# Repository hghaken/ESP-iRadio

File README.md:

# ESP32 Internet Radio

Battery-powered internet radio on an Olimex ESP32-DevKit-LiPo (WROVER, PSRAM): streams AAC/MP3 internet
radio over WiFi and plays it on Bluetooth headphones or a Bluetooth speaker (A2DP source), with a small colour TFT status
display (1.69" IPS, ST7789, 280x240: station logo, station, artist and song with scrolling for long lines,
Bluetooth link quality, buffer, WiFi signal, battery; high-contrast colours, no flicker; brightness,
night mode and idle dimming; a progress screen during firmware updates) and a web page for control,
configuration (up to 60 stations), diagnostics and firmware updates.

- Firmware: Arduino (C++) with PlatformIO. Build with `pio run`; update the running radio over WiFi with
  `pio run -t upload` (or upload `firmware.bin` on the web page). Serial flashing (`pio run -e usb -t upload`)
  is only needed once, for the OTA partition table. The firmware uses ~85% of an OTA slot (env `radio`) or ~74% (env `idf`); older
  builds are kept as git tags and in the git-ignored `backup/firmware/` for a quick rollback over WiFi.
- Live log: the web page has a "Log" section with an on/off switch that shows everything the radio
  also prints on the USB serial port (last ~64 KB kept, download as a text file), so the USB
  connector can stay on a power bank.
- Experimental: env `idf` builds Arduino as an ESP-IDF component with an own SDK configuration
  (`scripts/build_idf.ps1`, see `docs/framework-build.md`): classic Bluetooth only, no BLE/SPP/HFP,
  Bluetooth heap in PSRAM. ~74% of the OTA slot instead of ~85%, ~28 KB more free internal RAM. This
  is the build that runs on the radio. A larger TCP window was tried and did not work next to Bluetooth.
- First boot: join the access point `ESP-iRadio-Setup`, pick your WiFi network; afterwards use
  `http://radio.local/`.
- Bluetooth devices: up to 4 remembered (headphones, speakers), one plays at a time; play/pause on the device mutes, twice = next station, three times = previous. Pair a new
  one from the web page (device in pairing mode, type its name). Automatic mode tries them in the
  order you set (arrows); otherwise pick one with "Use" (restart, ~30 s). The radio reconnects
  with WiFi held off until the page finishes. "Try again" pages again and wipes nothing.
- SD card (microSD breakout on the SPI bus, CS GPIO4): daily log and measurement files with a chart
  on the web page, settings backup/restore, 64x64 station logos, copies of working firmware to roll
  back without a PC, and a year of history (events, listening and stream statistics per station,
  crash dumps) with tables on the web page.
- Rotary encoder (EC11): turn for volume (a bar on the display), press to mute, hold to choose a
  station.
- Line output and speaker: with Bluetooth switched off the radio plays on a PCM5102A I2S DAC
  (3.5 mm line out) and a MAX98357A I2S amplifier for a small speaker (web checkbox "Speaker").
- PCB: the KiCad project in `KiCad/` holds the schematic of an integrated board (ESP32-WROVER-IE,
  USB-C with charger and cell protection, display panel, DAC, amplifier, microSD, encoder, all
  parts assembled by JLCPCB); no board layout yet. See `KiCad/README.md`.
- WiFi: the radio reconnects to the mesh point it last used. A minute after every connect, and
  whenever the signal stays under a threshold on the web page (default -65 dBm), it looks for a
  point at least 12 dB stronger and moves there. The "Search" list shows every mesh point (channel,
  BSSID) with a "Switch to this access point" button. Opening the page does not scan
  for networks unless "Search networks when the page opens" is on. Setup mode always scans.
- Battery: 5000 mAh Li-Po (~28 h expected; a 2500 mAh cell ran ~14 h); level shown on the display
  and the web page.
- Stations: plain `http://` AAC-LC or MP3 streams (no TLS). About 25 Dutch stations (NPO, Radio 10,
  Veronica, Qmusic, Arrow) are verified; the URLs and the rules for finding working ones are in
  AGENTS.md under "Stations". Stations that are too heavy, HE-AAC only or https-only (Joe, NPO
  Sterren.nl, RadioNL, Team FM) run through Liquidsoap relays on a NAS (`nas/`) that re-encode
  them to AAC-LC 96 kbps on the own Icecast server.

All project knowledge - hardware, wiring, build and update commands, and the pitfalls learned the hard way
(internal RAM, flash budget, WiFi/Bluetooth coexistence, headphone pairing, brownouts) - lives in
[AGENTS.md](AGENTS.md).

## Hardware documentation

Not included in this repository (third-party documents); get them from the makers:
- Olimex ESP32-DevKit-LiPo: product page and user manual at https://www.olimex.com/Products/IoT/ESP32/ESP32-DevKit-LiPo/ ,
  schematics and KiCad files at https://github.com/OLIMEX/ESP32-DevKit-LiPo
  (`docs/olimex-jumpers-bottom.png` is drawn from that KiCad layout).
- 1.69" ST7789 IPS module (240x280, e.g. ZJY169S0800TG01) and a generic SPI microSD breakout.
- Sony WH-1000XM6 help guide: https://helpguide.sony.net/

## Credits and licence

Built with PlatformIO and the Arduino core for the ESP32, and these libraries:
[ESP32-A2DP](https://github.com/pschatzmann/ESP32-A2DP) (Apache-2.0),
[arduino-audio-tools](https://github.com/pschatzmann/arduino-audio-tools) (GPL-3.0),
[arduino-libhelix](https://github.com/pschatzmann/arduino-libhelix) (GPL-3.0, Helix AAC/MP3 decoders),
[Adafruit GFX](https://github.com/adafruit/Adafruit-GFX-Library) (BSD) and
[Adafruit ST7735 and ST7789](https://github.com/adafruit/Adafruit-ST7735-Library) (MIT).
The NAS relays use [Liquidsoap](https://www.liquidsoap.info/) and [Icecast](https://icecast.org/).

This project is licensed under the GNU General Public License v3.0, see [LICENSE](LICENSE).
Station URLs are examples of public Dutch broadcasters; host names such as `icecast.example.com`
and `my-nas` stand for your own servers.

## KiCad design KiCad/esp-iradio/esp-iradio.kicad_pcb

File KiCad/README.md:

# KiCad: PCB for the ESP iRadio

This folder holds everything an AI agent (Claude, Grok, ...) or a person needs to design a printed
circuit board for this radio in **KiCad 9**. The KiCad project is `esp-iradio/`: **schematic Rev B
of the integrated board** (2026-10-15, two A3 sheets in Elektuur/Elektor style, generated by the
scripts in `esp-iradio/tools/`; layout **Rev C** of 2026-10-16: 122 x 76 mm, 4 layers, autorouted,
DRC clean, for hand assembly (1206 passives) with display, encoder and connectors from top to
bottom, RCA outputs next to the 3.5 mm jack; the earlier 80 x 60 and 90 x 60 layouts (Rev B) were
reviewed by Grok and Claude). Its status, decisions, libraries and the
checks still open before the layout are in `esp-iradio/NOTES.md`.

## What the board is

Today the radio is a hand-wired stack: an **Olimex ESP32-DevKit-LiPo** (ESP32-WROVER, Li-Po charger,
USB) with jumper wires to a 1.69" ST7789 display. A rotary encoder, a microSD socket, a PCM5102A
DAC (line out) and a MAX98357A I2S amplifier (speaker) work on the breadboard (2026-10-15).

**Phase 1 (2026-10-11 .. 10-15, superseded): a carrier board.** The Olimex board plugs in on two
1x19 pin headers; the carrier holds the display, the encoder, the microSD socket, a PCM5102A DAC chip
(line out on a 3.5 mm jack), a mono class-D amplifier chip for one speaker, and a USB-C power
input. The firmware needs no pin changes: every net in `02-pinout-and-nets.md` matches
`src/config.h` and the docs. 2-layer board, assembled by JLCPCB; the ESP32 module and its charger
stay a finished product.

Owner decisions (2026-10-11, details in `01-requirements.md`): chips on the board (no audio
modules), display on the board, a 3D-printed case designed around the board, one mono speaker,
amplifier powered from a USB-C input, JLCPCB with SMT assembly.

**Phase 2 (chosen 2026-10-15, the current design, see `07-integrated-board.md`): an integrated
board** without breakouts: ESP32-WROVER-IE-N16R8 (external antenna on its U.FL), USB-C with a
CH340C, BQ24074 power-path charger with cell protection, 3.3 V LDO with the on/off switch, DAC,
amplifier, microSD and encoder, every part assembled by JLCPCB from stock; the display is the
HS20S010B module (2.0in, 320 x 240, LCSC C5329586) on two sockets, ordered loose in the same
JLCPCB/LCSC order (the bare 1.69in panel is not sold there). The owner chose to skip the carrier board. Documents 01-06 were written for
the carrier: their banners say what still applies.

## Files (read in this order)

| File | Content |
|---|---|
| `07-integrated-board.md` | **The current design input** (phase 2): owner decisions D8-D18, power (USB-C, BQ24074, cell protection, LDOs, switch), USB serial, WROVER-IE, display module, GPIO map, JLCPCB parts with LCSC numbers |
| `esp-iradio/NOTES.md` | Schematic Rev B: sheets, nets between them, chosen values, libraries, checks open before the layout |
| `esp-iradio/tools/README.md` | How the schematic is generated and checked (ERC, netlist check) |
| `06-checklist-and-bring-up.md` | Review checklist and bring-up: a section for the integrated board, then the carrier's |
| `01-requirements.md` | Scope, use cases and owner decisions D1-D7 (phase 1; most still hold) |
| `02-pinout-and-nets.md` | GPIO and net names (phase 1 headers; the GPIOs are the same on the integrated board, see 07) |
| `03-parts-and-footprints.md` | Phase 1 bill of materials (the integrated board's parts are in 07) |
| `04-power.md` | Phase 1 power tree (superseded by "Power" in 07) |
| `05-layout-guidelines.md` | Layout rules for the integrated board (rewritten 2026-10-15): mechanics, U.FL, 4 layers, USB pair, charger heat, audio and SPI routing, JLCPCB fab rules |

## Sources in this repository

- `AGENTS.md` (project root): the whole project, pin tables, pitfalls. Sections "Display wiring",
  "Battery measurement", "Hardware".
- `src/config.h`: the pins the firmware uses (`TFT_*`, `SD_CS`, `BAT_SENSE_PIN`, `PWR_SENSE_PIN`).
- `docs/speaker-output.md`: PCM5102A line out and MAX98357A speaker on the breadboard (pins, tests).
- `docs/display-research.md`: rotary encoder choice and pins.
- `docs/olimex-jumpers-bottom.png`: the three solder jumpers for battery/USB sensing on the Olimex board.
- Olimex ESP32-DevKit-LiPo **Rev.D** open hardware (KiCad sources, take the exact header
  positions, board outline and mounting holes from there):
  https://github.com/OLIMEX/ESP32-DevKit-LiPo/tree/master/HARDWARE

## Deliverables (when the design is done)

1. KiCad project `KiCad/esp-iradio/` (`.kicad_pro`, `esp-iradio.kicad_sch` + `power_usb.kicad_sch`,
   `.kicad_pcb`, project-local symbol/footprint libraries in `KiCad/esp-iradio/lib/`). Done so
   far: the schematic (Rev B).
2. Fabrication output in `KiCad/esp-iradio/fab/`: Gerbers + drill files, BOM (CSV with LCSC
   codes) and pick-and-place (CPL) file in JLCPCB's format.
3. For the 3D-printed case: a STEP of the assembled board and a DXF of the outline and holes in
   `KiCad/esp-iradio/case/`.
4. A short `KiCad/esp-iradio/NOTES.md`: design decisions, deviations from these documents, revision
   history (Rev A, B, ...).
5. If a pin changes: update `src/config.h`, `AGENTS.md`, the GPIO map in `07-integrated-board.md`
   and the schematic generator (`esp-iradio/tools/`) in the same step. The firmware and the board
   must never disagree.

## Tooling on the owner's PC (2026-10-11)

- **KiCad 9.0.9** (`C:\Program Files\KiCad\9.0`). Chosen over EasyEDA Pro for git-friendly text
  files and AI access; JLCPCB output comes from plugins.
- **KiCad MCP server** for Claude Code: mixelpixx/KiCAD-MCP-Server v2.8.2 (branch `stable`, MIT),
  cloned to `C:\Users\Admin\mcp-servers\KiCAD-MCP-Server`. Python: a venv in that folder (`venv\`,
  made from KiCad's own Python 3.11 with `--system-site-packages`, so `pcbnew` imports and the KiCad
  install itself stays untouched) with `requirements.txt`; the server finds the venv by itself.
  Node 24, `npm install` + `npm run build` -> `dist\index.js`. Registered in Claude Code at user
  scope as `kicad` (`claude mcp add kicad --scope user -e KICAD_AUTO_LAUNCH=false ... -- node
  ...\dist\index.js`); the tools appear in a new Claude Code session. Update: `git pull` in that
  folder, `npm run build`, `venv\Scripts\python -m pip install -r requirements.txt`.
- Pitfall: the server writes new sheets in the KiCad 10 file format, which KiCad 9 skips
  without an error (empty netlist). Its templates are patched to KiCad 9 on this PC; details and
  the fix in `esp-iradio/NOTES.md` ("Tooling pitfall"). Check every change with
  `kicad-cli sch export netlist` (component count) and `kicad-cli sch erc`.
- Optional, for live sync with an open KiCad window: KiCad -> Preferences -> Plugins -> enable
  the KiCad API (IPC). The file-based tools work without it.
- Installed in KiCad (Plugin and Content Manager): **kicad-jlcpcb-tools** (LCSC part search with
  stock, `LCSC` fields, JLCPCB BOM/CPL export; its parts database
  `E:\Documents\KiCad\9.0\3rdparty\plugins\com_github_bouni_kicad-jlcpcb-tools\jlcpcb\current-parts-fts5.db`
  is plain SQLite and can be queried read-only by a script). **easyeda2kicad** 1.0.1 (symbol,
  footprint and 3D model of an LCSC part) runs from a Python venv: `easyeda2kicad --lcsc_id
  C701352 --full --output <dir>/lcsc`; the project copy is `esp-iradio/lib/lcsc.*`.
- Rev B (schematic and first layout) was not drawn with the MCP server but generated by
  `esp-iradio/tools/` (Python; the board scripts run with KiCad's own Python, see its README).
- Autorouter: Freerouting 1.9.0 (`C:\Users\Admin\tools\freerouting-1.9.0.jar`) on a portable
  Java 21 (`C:\Users\Admin\tools\jdk-21.0.12.1+1-jre`), downloaded with the owner's consent
  2026-10-15. Freerouting 2.x jars need Java 25; the 2.5.0 native CLI crashed while routing.
- 3D models: this PC's KiCad install lacks some 3D folders (`Connector_USB`, `Rotary_Encoder`);
  install them before the STEP export for the case.

## Commands (`kicad-cli`, run inside `esp-iradio/`)

`C:\Program Files\KiCad\9.0\bin\kicad-cli.exe`:
- ERC: `kicad-cli sch erc --severity-all -o erc.rpt esp-iradio.kicad_sch`
- Netlist (check the component count after every schematic change):
  `kicad-cli sch export netlist --format kicadsexpr -o esp-iradio.net esp-iradio.kicad_sch`, then
  `python tools/intcheck.py esp-iradio.net` (expected connections of the integrated board)
- Schematic PDF/SVG: `kicad-cli sch export pdf esp-iradio.kicad_sch` (or `export svg -o <dir>`)
- DRC: `kicad-cli pcb drc esp-iradio.kicad_pcb`
- JLCPCB order files (Gerber zip, BOM, CPL): `"C:/Program Files/KiCad/9.0/bin/python.exe"
  tools/jlcfab.py` writes them to `esp-iradio/jlcpcb/` (see the README there).
- STEP for the case: `kicad-cli pcb export step esp-iradio.kicad_pcb -o case/esp-iradio.step`

Close the schematic/board in KiCad (or reload afterwards) before an agent edits the files: KiCad
overwrites external changes; `*.lck` files mean KiCad has them open. Only one agent session works
on the KiCad project at a time.

## Rules for agents

- Do not invent part numbers, LCSC codes or module dimensions: look them up (datasheet, supplier
  page) or mark them `TBD` and list them under open questions.
- Ask the owner before ordering anything or choosing between options marked "owner decides".
- Everything in this folder is English; talk to the owner in Dutch.

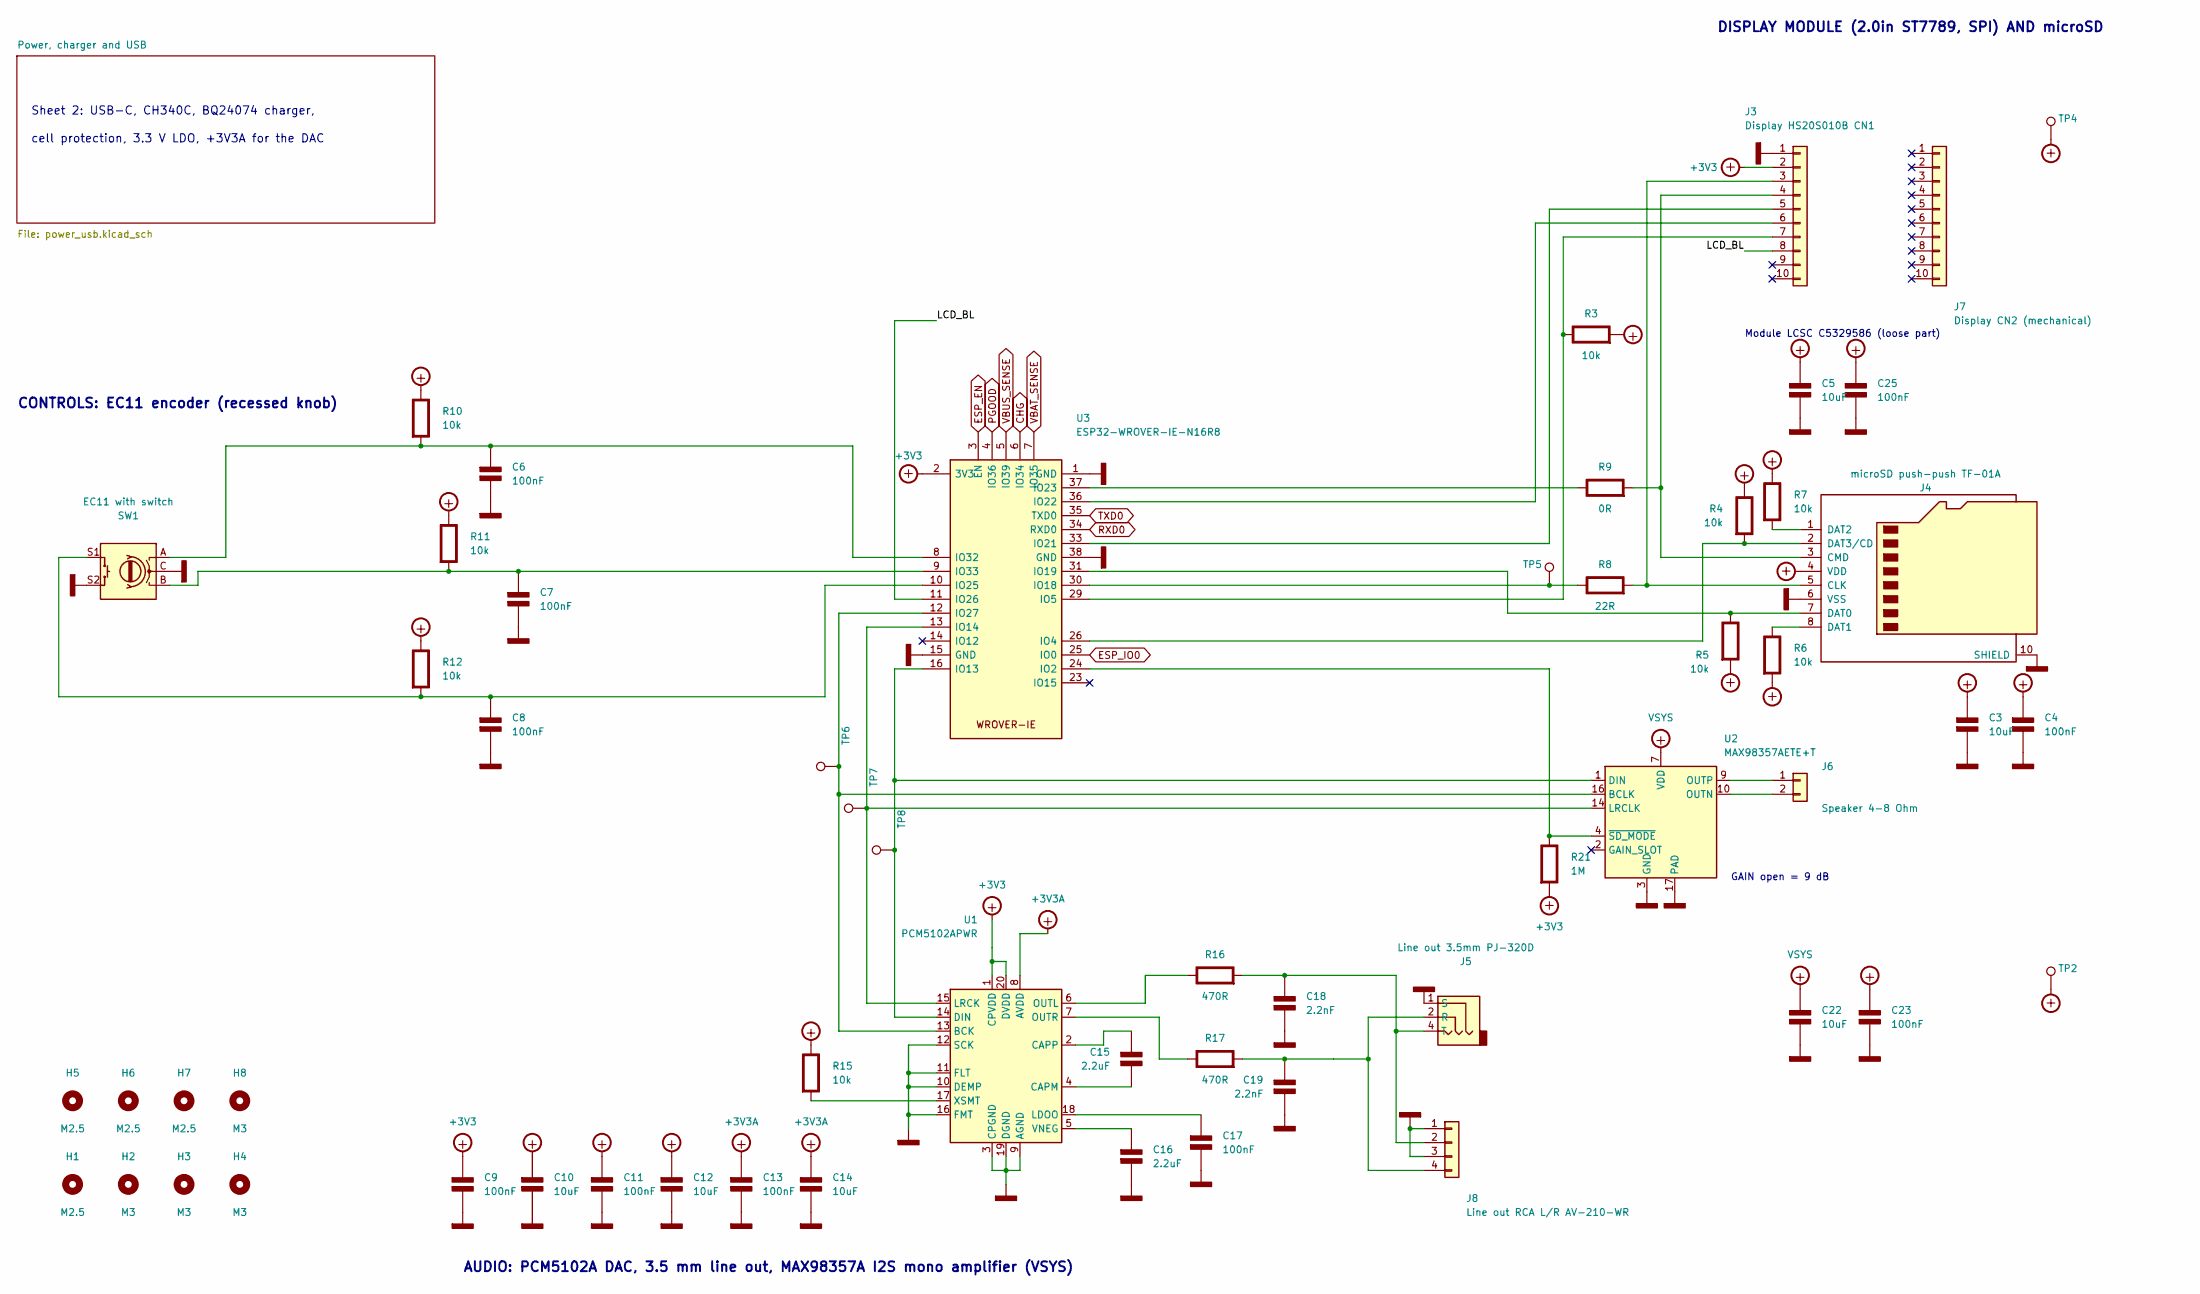
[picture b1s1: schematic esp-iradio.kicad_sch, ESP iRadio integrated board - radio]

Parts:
C3, C5, C10, C12, C14, C22: 10uF; C_1206_3216Metric
C4, C6, C7, C8, C9, C11, C13, C17, C23, C25: 100nF; C_1206_3216Metric
C15, C16: 2.2uF; C_1206_3216Metric
C18, C19: 2.2nF; C_1206_3216Metric
H1, H5, H6, H7: M2.5; MountingHole_2.7mm_M2.5
H2, H3, H4, H8: M3; MountingHole_3.2mm_M3
J3: Display HS20S010B CN1; PinSocket_1x10_P2.54mm_Vertical_HS20S010B; LCSC C2897373
J4: microSD push-push TF-01A; TF-SMD_TF-01A; LCSC C91145
J5: Line out 3.5mm PJ-320D; AUDIO-SMD_PJ-320D-1; LCSC C431535
J6: Speaker 4-8 Ohm; TerminalBlock_MaiXu_MX126-5.0-02P_1x02_P5.00mm; LCSC C8404
J7: Display CN2 (mechanical); PinSocket_1x10_P2.54mm_Vertical; LCSC C2897373
J8: Line out RCA L/R AV-210-WR; RCA-TH_AV-210-WR; LCSC C53431212
R3, R4, R5, R6, R7, R10, R11, R12, R15: 10k; R_1206_3216Metric
R8: 22R; R_1206_3216Metric
R9: 0R; R_1206_3216Metric
R16, R17: 470R; R_1206_3216Metric
R21: 1M; R_1206_3216Metric
SW1: EC11 with switch; RotaryEncoder_Alps_EC11E-Switch_Vertical_H20mm
TP2: VSYS; TestPoint_Pad_D1.5mm
TP4: +3V3; TestPoint_Pad_D1.5mm
TP5: SPI_SCK; TestPoint_Pad_D1.5mm
TP6: I2S_BCK; TestPoint_Pad_D1.5mm
TP7: I2S_LRCK; TestPoint_Pad_D1.5mm
TP8: I2S_DATA; TestPoint_Pad_D1.5mm
U1: PCM5102APWR; TSSOP-20_4.4x6.5mm_P0.65mm; LCSC C107671
U2: MAX98357AETE+T; TQFN-16-1EP_3x3mm_P0.5mm_EP1.23x1.23mm_ThermalVias; LCSC C910544
U3: ESP32-WROVER-IE-N16R8; ESP32-WROVER-IE_SMD; LCSC C701352

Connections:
+3V3: C3.1 (+), C4.1 (+), C5.1 (+), C9.1 (+), C10.1 (+), C11.1 (+), C12.1 (+), C25.1 (+), J3.2, J4.4 (VDD), R3.2 (-), R4.1 (+), R5.2 (-), R6.2 (-), R7.1 (+), R10.1 (+), R11.1 (+), R12.1 (+), R15.1 (+), R21.2 (-), TP4.1, U1.1 (CPVDD), U1.20 (DVDD), U3.2 (3V3); also elsewhere on the board
+3V3A: C13.1 (+), C14.1 (+), U1.8 (AVDD); also elsewhere on the board
/LCD_BL: J3.8, U3.11 (IO26)
CHG: U3.6 (IO34); also elsewhere on the board
ESP_EN: U3.3 (EN); also elsewhere on the board
ESP_IO0: U3.25 (IO0); also elsewhere on the board
GND: C3.2 (-), C4.2 (-), C5.2 (-), C6.2 (-), C7.2 (-), C8.2 (-), C9.2 (-), C10.2 (-), C11.2 (-), C12.2 (-), C13.2 (-), C14.2 (-), C16.2 (-), C17.2 (-), C18.2 (-), C19.2 (-), C22.2 (-), C23.2 (-), C25.2 (-), J3.1, J4.6 (VSS), J4.10 (SHIELD), J4.11 (SHIELD), J4.12 (SHIELD), J4.13 (SHIELD), J5.1 (S), J8.1, J8.3, SW1.C, SW1.S2, U1.3 (CPGND), U1.9 (AGND), U1.10 (DEMP), U1.11 (FLT), U1.12 (SCK), U1.16 (FMT), U1.19 (DGND), U2.3 (GND), U2.11 (GND), U2.15 (GND), U2.17 (PAD), U3.1 (GND), U3.15 (GND), U3.38 (GND), U3.39 (GND); also elsewhere on the board
unnamed: C6.1 (+), R10.2 (-), SW1.A, U3.8 (IO32)
unnamed: C7.1 (+), R11.2 (-), SW1.B, U3.9 (IO33)
unnamed: C8.1 (+), R12.2 (-), SW1.S1, U3.10 (IO25)
unnamed: C15.1 (+), U1.2 (CAPP)
unnamed: C15.2 (-), U1.4 (CAPM)
unnamed: C16.1 (+), U1.5 (VNEG)
unnamed: C17.1 (+), U1.18 (LDOO)
unnamed: C18.1 (+), J5.4 (T), J8.2, R16.2 (-)
unnamed: C19.1 (+), J5.2 (R), J8.4, R17.2 (-)
unnamed: J3.3, J4.5 (CLK), R8.2 (-)
unnamed: J3.4, J4.3 (CMD), R9.2 (-)
unnamed: J3.5, U3.33 (IO21)
unnamed: J3.6, U3.36 (IO22)
unnamed: J3.7, R3.1 (+), U3.29 (IO5)
unnamed: J4.7 (DAT0), R5.1 (+), U3.31 (IO19)
unnamed: J4.8 (DAT1), R6.1 (+)
unnamed: J4.1 (DAT2), R7.2 (-)
unnamed: J4.2 (DAT3/CD), R4.2 (-), U3.26 (IO4)
unnamed: J6.1, U2.9 (OUTP)
unnamed: J6.2, U2.10 (OUTN)
unnamed: R8.1 (+), TP5.1, U3.30 (IO18)
unnamed: R9.1 (+), U3.37 (IO23)
unnamed: R15.2 (-), U1.17 (XSMT)
unnamed: R16.1 (+), U1.6 (OUTL)
unnamed: R17.1 (+), U1.7 (OUTR)
unnamed: R21.1 (+), U2.4 (~SD_MODE), U3.24 (IO2)
unnamed: TP6.1, U1.13 (BCK), U2.16 (BCLK), U3.12 (IO27)
unnamed: TP8.1, U1.14 (DIN), U2.1 (DIN), U3.16 (IO13)
unnamed: TP7.1, U1.15 (LRCK), U2.14 (LRCLK), U3.13 (IO14)
PGOOD: U3.4 (IO36); also elsewhere on the board
RXD0: U3.34 (RXD0); also elsewhere on the board
TXD0: U3.35 (TXD0); also elsewhere on the board
VBAT_SENSE: U3.7 (IO35); also elsewhere on the board
VBUS_SENSE: U3.5 (IO39); also elsewhere on the board
VSYS: C22.1 (+), C23.1 (+), TP2.1, U2.7 (VDD), U2.8 (VDD); also elsewhere on the board

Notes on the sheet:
Sheet 2: USB-C, CH340C, BQ24074 charger,
cell protection, 3.3 V LDO, +3V3A for the DAC
CONTROLS: EC11 encoder (recessed knob)
Module LCSC C5329586 (loose part)
DISPLAY MODULE (2.0in ST7789, SPI) AND microSD
GAIN open = 9 dB
AUDIO: PCM5102A DAC, 3.5 mm line out, MAX98357A I2S mono amplifier (VSYS)

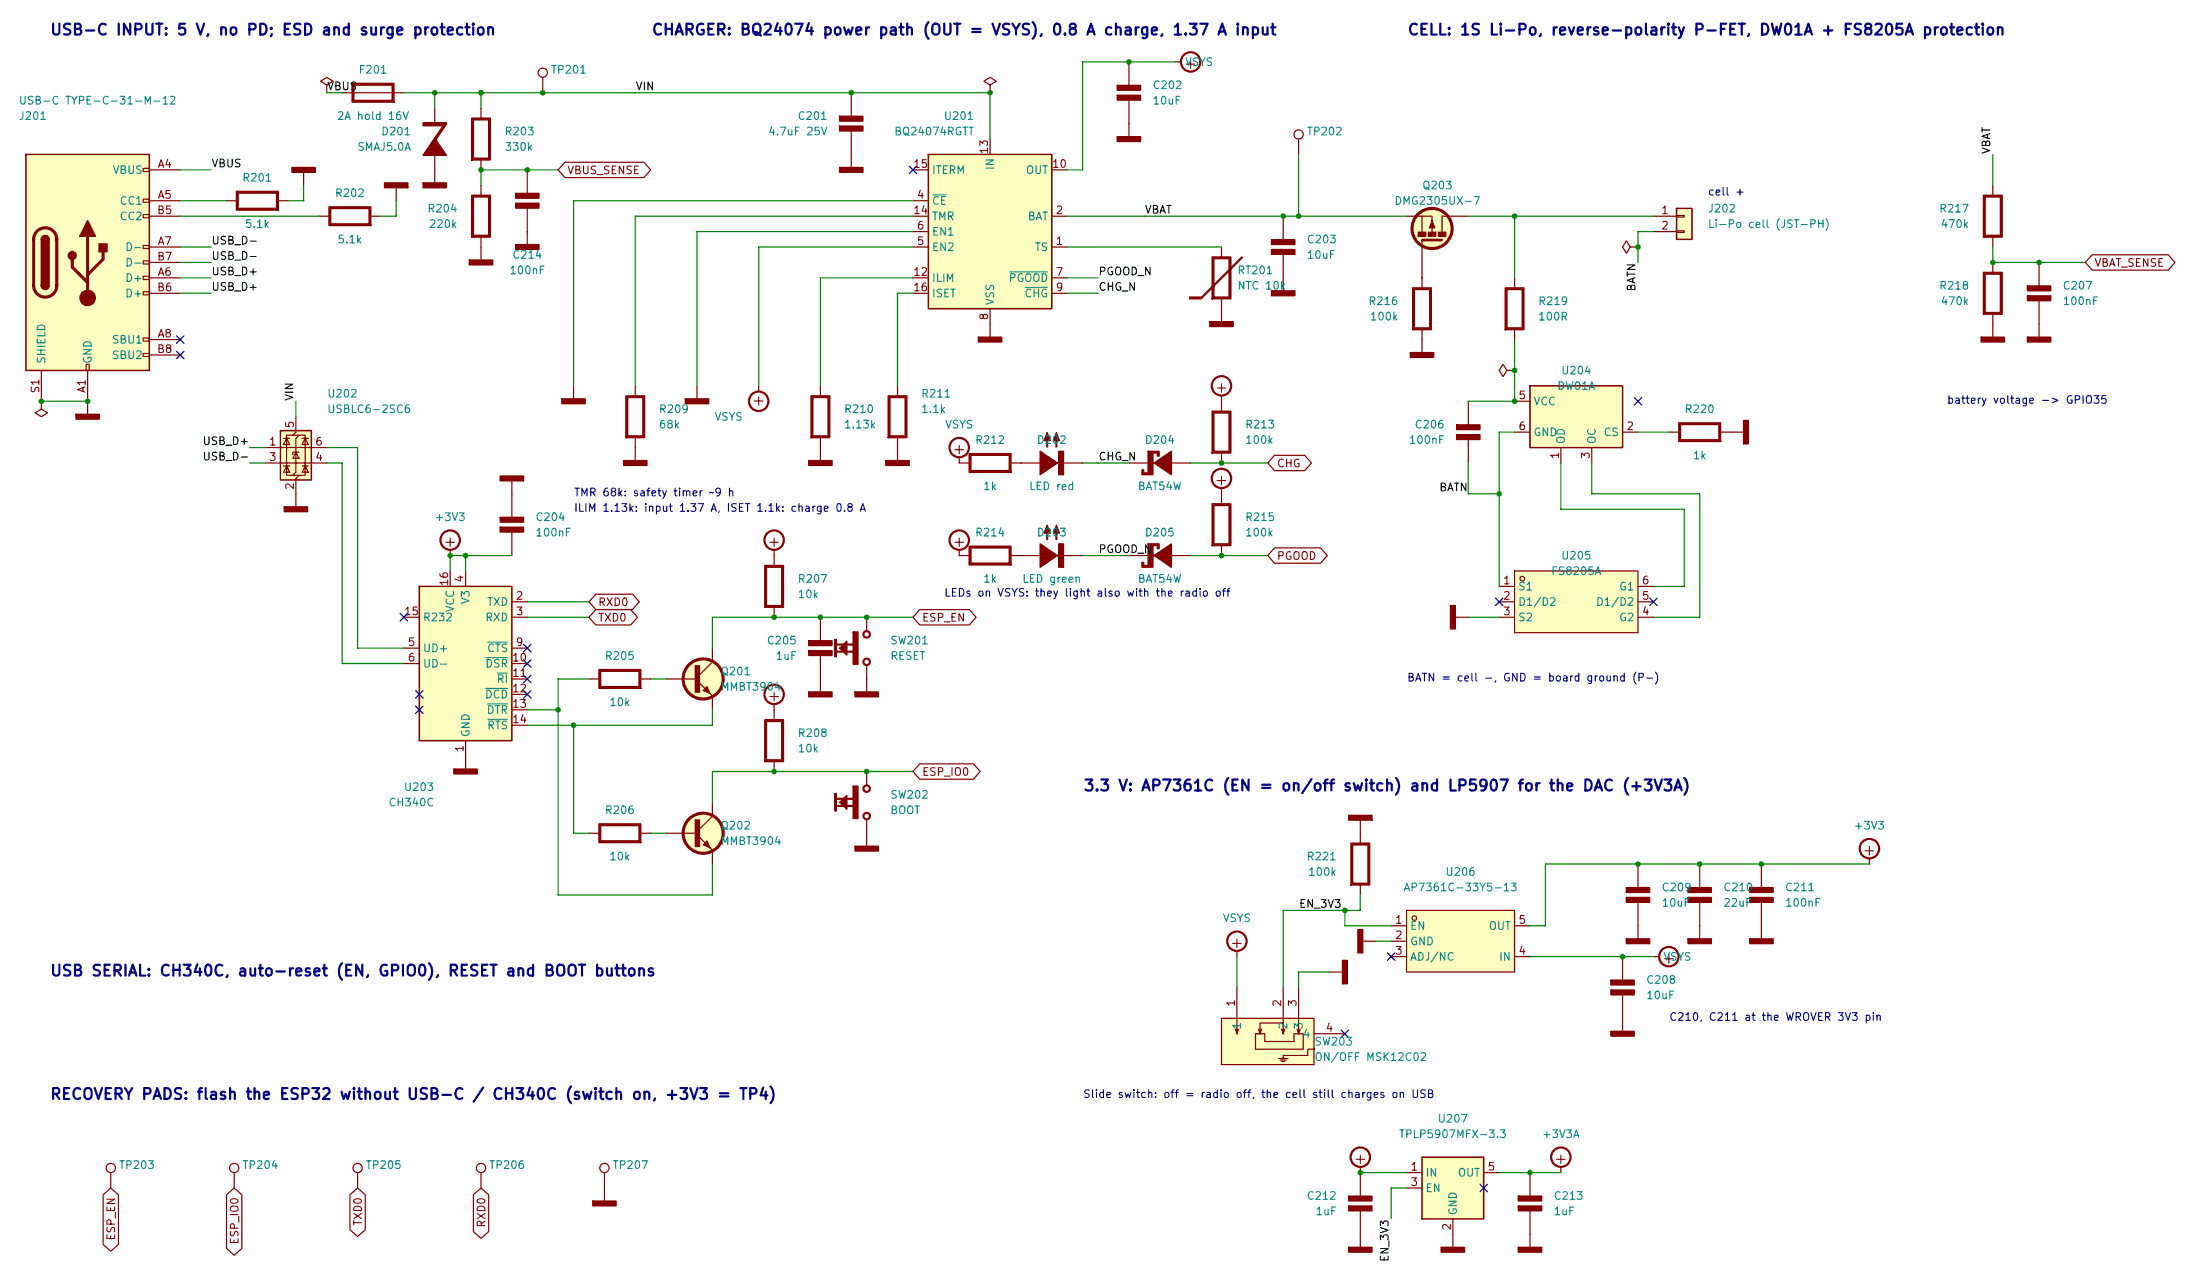
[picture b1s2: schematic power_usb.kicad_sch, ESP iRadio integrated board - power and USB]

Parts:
C201: 4.7uF 25V; C_1206_3216Metric
C202, C203, C208, C209: 10uF; C_1206_3216Metric
C204, C206, C207, C211, C214: 100nF; C_1206_3216Metric
C205, C212, C213: 1uF; C_1206_3216Metric
C210: 22uF; C_1206_3216Metric
D201: SMAJ5.0A; D_SMA; LCSC C113952
D202: LED red; LED_1206_3216Metric; LCSC C965822
D203: LED green; LED_1206_3216Metric; LCSC C965825
D204, D205: BAT54W; D_SOD-123; LCSC C7502705
F201: 2A hold 16V; Fuse_1206_3216Metric; LCSC C22374899
J201: USB-C TYPE-C-31-M-12; USB_C_Receptacle_HRO_TYPE-C-31-M-12; LCSC C165948
J202: Li-Po cell (JST-PH); JST_PH_B2B-PH-K_1x02_P2.00mm_Vertical; LCSC C131337
Q201, Q202: MMBT3904; SOT-23; LCSC C7420353
Q203: DMG2305UX-7; SOT-23; LCSC C5261054
R201, R202: 5.1k; R_1206_3216Metric
R203: 330k; R_1206_3216Metric
R204: 220k; R_1206_3216Metric
R205, R206, R207, R208: 10k; R_1206_3216Metric
R209: 68k; R_1206_3216Metric
R210: 1.13k; R_1206_3216Metric
R211: 1.1k; R_1206_3216Metric
R212, R214, R220: 1k; R_1206_3216Metric
R213, R215, R216, R221: 100k; R_1206_3216Metric
R217, R218: 470k; R_1206_3216Metric
R219: 100R; R_1206_3216Metric
RT201: NTC 10k; R_0805_2012Metric; LCSC C2889056
SW201: RESET; SW_TS-1187A; LCSC C318884
SW202: BOOT; SW_TS-1187A; LCSC C318884
SW203: ON/OFF MSK12C02; SW-TH_MSK12C02; LCSC C431540
TP201: VIN; TestPoint_Pad_D1.5mm
TP202: VBAT; TestPoint_Pad_D1.5mm
TP203: ESP_EN; TestPoint_Pad_D1.5mm
TP204: ESP_IO0; TestPoint_Pad_D1.5mm
TP205: TXD0; TestPoint_Pad_D1.5mm
TP206: RXD0; TestPoint_Pad_D1.5mm
TP207: GND; TestPoint_Pad_D1.5mm
U201: BQ24074RGTT; VQFN-16-1EP_3x3mm_P0.5mm_EP1.68x1.68mm_ThermalVias; LCSC C2861252
U202: USBLC6-2SC6; SOT-23-6; LCSC C2827654
U203: CH340C; SOIC-16_3.9x9.9mm_P1.27mm; LCSC C84681
U204: DW01A; SOT-23-6; LCSC C351410
U205: FS8205A; SOT-23-6_L2.9-W1.6-P0.95-LS2.8-BR; LCSC C2830320
U206: AP7361C-33Y5-13; SOT-89-5_L4.5-W2.5-P1.50-LS4.5-BR; LCSC C460397
U207: TPLP5907MFX-3.3; SOT-23-5; LCSC C5370990

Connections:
+3V3: C204.2 (-), C209.1 (+), C210.1 (+), C211.1 (+), R207.1 (+), R208.1 (+), R213.1 (+), R215.1 (+), U203.4 (V3), U203.16 (VCC), U206.5 (OUT); also elsewhere on the board
+3V3A: C213.1 (+), U207.5 (OUT); also elsewhere on the board
/Power, charger and USB/BATN: C206.2 (-), J202.2, U204.6 (GND), U205.1 (S1)
/Power, charger and USB/CHG_N: D202.1 (K-), D204.1 (K-), U201.9 (~CHG)
/Power, charger and USB/EN_3V3: R221.2 (-), SW203.2, U206.1 (EN), U207.3 (EN)
/Power, charger and USB/PGOOD_N: D203.1 (K-), D205.1 (K-), U201.7 (~PGOOD)
/Power, charger and USB/USB_D+: J201.A6 (D+), J201.B6 (D+), U202.1 (I/O1)
/Power, charger and USB/USB_D-: J201.A7 (D-), J201.B7 (D-), U202.3 (I/O2)
/Power, charger and USB/VBAT: C203.1 (+), Q203.2 (S), R217.1 (+), TP202.1, U201.2 (BAT), U201.3 (BAT)
/Power, charger and USB/VBUS: F201.1 (+), J201.A4 (VBUS), J201.A9 (VBUS), J201.B4 (VBUS), J201.B9 (VBUS)
/Power, charger and USB/VIN: C201.1 (+), D201.1 (K-), F201.2 (-), R203.1 (+), TP201.1, U201.13 (IN), U202.5 (VBUS)
CHG: D204.2 (A+), R213.2 (-); also elsewhere on the board
ESP_EN: C205.1 (+), Q201.3 (C), R207.2 (-), SW201.4, TP203.1; also elsewhere on the board
ESP_IO0: Q202.3 (C), R208.2 (-), SW202.4, TP204.1; also elsewhere on the board
GND: C201.2 (-), C202.2 (-), C203.2 (-), C204.1 (+), C205.2 (-), C207.2 (-), C208.2 (-), C209.2 (-), C210.2 (-), C211.2 (-), C212.2 (-), C213.2 (-), C214.2 (-), D201.2 (A+), J201.A1 (GND), J201.A12 (GND), J201.B1 (GND), J201.B12 (GND), J201.S1 (SHIELD), R201.2 (-), R202.2 (-), R204.2 (-), R209.2 (-), R210.2 (-), R211.2 (-), R216.2 (-), R218.2 (-), R220.2 (-), R221.1 (+), RT201.2 (-), SW201.3, SW202.3, SW203.3, TP207.1, U201.4 (~CE), U201.6 (EN1), U201.8 (VSS), U201.17 (VSS), U202.2 (GND), U203.1 (GND), U205.3 (S2), U206.2 (GND), U207.2 (GND); also elsewhere on the board
unnamed: C206.1 (+), R219.2 (-), U204.5 (VCC)
unnamed: D202.2 (A+), R212.2 (-)
unnamed: D203.2 (A+), R214.2 (-)
unnamed: J201.A5 (CC1), R201.1 (+)
unnamed: J201.B5 (CC2), R202.1 (+)
unnamed: J202.1, Q203.3 (D), R219.1 (+)
unnamed: Q201.1 (B), R205.2 (-)
unnamed: Q201.2 (E), R206.1 (+), U203.14 (~RTS)
unnamed: Q202.1 (B), R206.2 (-)
unnamed: Q202.2 (E), R205.1 (+), U203.13 (~DTR)
unnamed: Q203.1 (G), R216.1 (+)
unnamed: R209.1 (+), U201.14 (TMR)
unnamed: R210.1 (+), U201.12 (ILIM)
unnamed: R211.1 (+), U201.16 (ISET)
unnamed: R220.1 (+), U204.2 (CS)
unnamed: RT201.1 (+), U201.1 (TS)
unnamed: U202.6 (I/O1), U203.5 (UD+)
unnamed: U202.4 (I/O2), U203.6 (UD-)
unnamed: U204.3 (OC), U205.4 (G2)
unnamed: U204.1 (OD), U205.6 (G1)
PGOOD: D205.2 (A+), R215.2 (-); also elsewhere on the board
RXD0: TP206.1, U203.2 (TXD); also elsewhere on the board
TXD0: TP205.1, U203.3 (RXD); also elsewhere on the board
VBAT_SENSE: C207.1 (+), R217.2 (-), R218.1 (+); also elsewhere on the board
VBUS_SENSE: C214.1 (+), R203.2 (-), R204.1 (+); also elsewhere on the board
VSYS: C202.1 (+), C208.1 (+), C212.1 (+), R212.1 (+), R214.1 (+), SW203.1, U201.5 (EN2), U201.10 (OUT), U201.11 (OUT), U206.4 (IN), U207.1 (IN); also elsewhere on the board

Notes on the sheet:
USB-C INPUT: 5 V, no PD; ESD and surge protection
USB SERIAL: CH340C, auto-reset (EN, GPIO0), RESET and BOOT buttons
RECOVERY PADS: flash the ESP32 without USB-C / CH340C (switch on, +3V3 = TP4)
CHARGER: BQ24074 power path (OUT = VSYS), 0.8 A charge, 1.37 A input
TMR 68k: safety timer ~9 h
ILIM 1.13k: input 1.37 A, ISET 1.1k: charge 0.8 A
LEDs on VSYS: they light also with the radio off
CELL: 1S Li-Po, reverse-polarity P-FET, DW01A + FS8205A protection
battery voltage -> GPIO35
cell +
BATN = cell -, GND = board ground (P-)
3.3 V: AP7361C (EN = on/off switch) and LP5907 for the DAC (+3V3A)
C210, C211 at the WROVER 3V3 pin
Slide switch: off = radio off, the cell still charges on USB

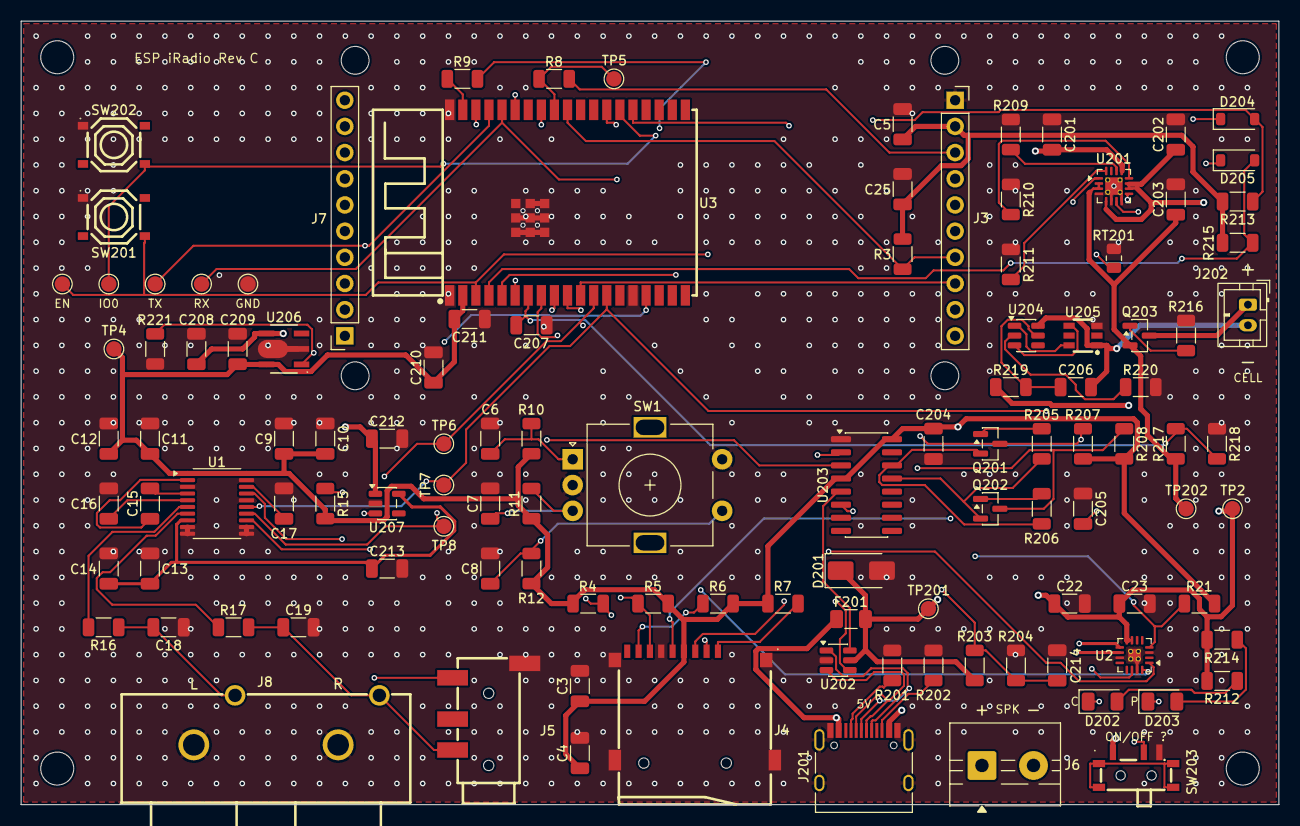
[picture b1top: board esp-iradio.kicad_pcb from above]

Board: 4 copper layers, 122.0 x 76.0 mm, 122 parts (0 on the bottom side), 71 nets.

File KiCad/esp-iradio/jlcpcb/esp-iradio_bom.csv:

Comment,Designator,Footprint,LCSC Part #,Quantity
10uF,"C3,C5,C10,C12,C14,C22,C202,C203,C208,C209",C_1206_3216Metric,C13585,10
100nF,"C4,C6,C7,C8,C9,C11,C13,C17,C23,C25,C204,C206,C207,C211,C214",C_1206_3216Metric,C24497,15
2.2uF,"C15,C16",C_1206_3216Metric,C50254,2
2.2nF,"C18,C19",C_1206_3216Metric,C9191,2
4.7uF 25V,C201,C_1206_3216Metric,C29823,1
1uF,"C205,C212,C213",C_1206_3216Metric,C1848,3
22uF,C210,C_1206_3216Metric,C12891,1
SMAJ5.0A,D201,D_SMA,C113952,1
LED red,D202,LED_1206_3216Metric,C965822,1
LED green,D203,LED_1206_3216Metric,C965825,1
BAT54W,"D204,D205",D_SOD-123,C7502705,2
2A hold 16V,F201,Fuse_1206_3216Metric,C22374899,1
Display HS20S010B CN1,J3,PinSocket_1x10_P2.54mm_Vertical_HS20S010B,C2897373,1
microSD push-push TF-01A,J4,TF-SMD_TF-01A,C91145,1
Line out 3.5mm PJ-320D,J5,AUDIO-SMD_PJ-320D-1,C431535,1
Speaker 4-8 Ohm,J6,TerminalBlock_MaiXu_MX126-5.0-02P_1x02_P5.00mm,C8404,1
Display CN2 (mechanical),J7,PinSocket_1x10_P2.54mm_Vertical,C2897373,1
Line out RCA L/R AV-210-WR,J8,RCA-TH_AV-210-WR,C53431212,1
USB-C TYPE-C-31-M-12,J201,USB_C_Receptacle_HRO_TYPE-C-31-M-12,C165948,1
Li-Po cell (JST-PH),J202,JST_PH_B2B-PH-K_1x02_P2.00mm_Vertical,C131337,1
MMBT3904,"Q201,Q202",SOT-23,C7420353,2
DMG2305UX-7,Q203,SOT-23,C5261054,1
10k,"R3,R4,R5,R6,R7,R10,R11,R12,R15,R205,R206,R207,R208",R_1206_3216Metric,C17902,13
22R,R8,R_1206_3216Metric,C17958,1
0R,R9,R_1206_3216Metric,C17888,1
470R,"R16,R17",R_1206_3216Metric,C2933707,2
1M,R21,R_1206_3216Metric,C17927,1
5.1k,"R201,R202",R_1206_3216Metric,C2933721,2
330k,R203,R_1206_3216Metric,C17929,1
220k,R204,R_1206_3216Metric,C2933643,1
68k,R209,R_1206_3216Metric,C2933748,1
1.13k,R210,R_1206_3216Metric,C5204018,1
1.1k,R211,R_1206_3216Metric,C2933580,1
1k,"R212,R214,R220",R_1206_3216Metric,C4410,3
100k,"R213,R215,R216,R221",R_1206_3216Metric,C17900,4
470k,"R217,R218",R_1206_3216Metric,C2933709,2
100R,R219,R_1206_3216Metric,C17901,1
NTC 10k,RT201,R_0805_2012Metric,C2889056,1
EC11 with switch,SW1,RotaryEncoder_Alps_EC11E-Switch_Vertical_H20mm,,1
RESET / BOOT,"SW201,SW202",SW_TS-1187A,C318884,2
ON/OFF MSK12C02,SW203,SW-TH_MSK12C02,C431540,1
PCM5102APWR,U1,TSSOP-20_4.4x6.5mm_P0.65mm,C107671,1
MAX98357AETE+T,U2,TQFN-16-1EP_3x3mm_P0.5mm_EP1.23x1.23mm_ThermalVias,C910544,1
ESP32-WROVER-IE-N16R8,U3,ESP32-WROVER-IE_SMD,C701352,1
BQ24074RGTT,U201,VQFN-16-1EP_3x3mm_P0.5mm_EP1.68x1.68mm_ThermalVias,C2861252,1
USBLC6-2SC6,U202,SOT-23-6,C2827654,1
CH340C,U203,SOIC-16_3.9x9.9mm_P1.27mm,C84681,1
DW01A,U204,SOT-23-6,C351410,1
FS8205A,U205,SOT-23-6_L2.9-W1.6-P0.95-LS2.8-BR,C2830320,1
AP7361C-33Y5-13,U206,SOT-89-5_L4.5-W2.5-P1.50-LS4.5-BR,C460397,1
TPLP5907MFX-3.3,U207,SOT-23-5,C5370990,1

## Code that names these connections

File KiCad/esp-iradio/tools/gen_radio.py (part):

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gnd(Rt(1), 'right')
gnd(Rt(7), 'right')
# to the power/USB sheet
for pin, net in (('3', 'ESP_EN'), ('4', 'PGOOD'), ('5', 'VBUS_SENSE'), ('6', 'CHG'), ('7', 'VBAT_SENSE')):
    s.glabel(net, P('U3', pin), 90)
s.glabel('TXD0', Rt(4), 0)
s.glabel('RXD0', Rt(5), 0)
s.glabel('ESP_IO0', Rt(14), 0)

# ---------------------------------------------------------------- power sheet (top left)
s.sheet_symbol('Power, charger and USB', 'power_usb.kicad_sch', (20.32, 35.56), (76.2, 30.48), POWER_SHEET_UUID, '2')
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W(Rt(10), (302.26, Rt(10)[1]), (302.26, 86.36), (302.26, P('J3', 7)[1]), P('J3', 7))
R('R3', 307.34, 86.36, '10k', 90)
right('+3V3', P('R3', 2), False)
# LCD_BL from IO26 to the module's BLK pin (CN1 pin 8): labels, the signal columns are in the way
W(L(10), (180.34, L(10)[1]), (180.34, 83.82), (187.96, 83.82))
s.label('LCD_BL', (187.96, 83.82))
W(P('J3', 8), (335.28, P('J3', 8)[1]))
s.label('LCD_BL', (335.28, P('J3', 8)[1]), 180)
# MISO -> J4 DAT0 + R5
W(Rt(8), (292.1, Rt(8)[1]), (292.1, 137.16), (332.74, 137.16), P('J4', 'DAT0'))
R('R5', 332.74, 142.24, '10k', fields={'ref': (328.93, 144.78, 0, 'right'), 'val': (328.93, 147.32, 0, 'right')})
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
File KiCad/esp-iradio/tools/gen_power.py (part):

"""ESP iRadio integrated board, sheet 2: USB-C, USB serial (CH340C) with auto-reset, BQ24074 power-path
charger, cell protection, 3.3 V and 3.3 V analog regulators with the on/off switch. Elektuur style.
Connects to the radio sheet through global labels and the global power nets (VSYS, +3V3, +3V3A, GND)."""
import os, sys
sys.path.insert(0, os.path.dirname(os.path.abspath(__file__)))
from schgen import Libs, Sheet
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C('C214', 99.06, P('R203', 2)[1] + 5.08, '100nF',
  fields={'ref': (99.06, P('R203', 2)[1] + 13.97, 0, None), 'val': (99.06, P('R203', 2)[1] + 16.51, 0, None)})
gnd(P('C214', 2))
s.glabel('VBUS_SENSE', (104.14, P('R203', 2)[1]), 0)
gnd(P('R204', 2))

# USB ESD: USBLC6-2SC6
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s.add('Elektuur:S-make-push', 'SW201', 154.94, ENY + 5.08, 0, 'RESET', 'esp-iradio:SW_TS-1187A',
      extra={'LCSC': 'C318884'})
gnd(P('SW201', '3'))
s.glabel('ESP_EN', (162.56, ENY), 0)
# GPIO0: 10k up, BOOT button
IOY = P('Q202', 'C')[1] - 5.08
W(P('Q202', 'C'), (P('Q202', 'C')[0], IOY), (162.56, IOY))
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s.add('Elektuur:S-make-push', 'SW202', 154.94, IOY + 5.08, 0, 'BOOT', 'esp-iradio:SW_TS-1187A',
      extra={'LCSC': 'C318884'})
gnd(P('SW202', '3'))
s.glabel('ESP_IO0', (162.56, IOY), 0)

# recovery pads: flash the ESP32 with a serial adapter when USB-C or the CH340C is dead (switch on;
# +3V3 is TP4 on sheet 1)
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gnd(P('R218', 2))
gnd(P('C207', 2))
W(P('C207', 1), (VX + 15.24, tap[1]))
s.glabel('VBAT_SENSE', (VX + 15.24, tap[1]), 0)
s.text('battery voltage -> GPIO35', (VX - 7.62, 91.44), 1.27, False)
tp('TP202', (226.06, 50.8), 'VBAT')
W((226.06, 50.8), (226.06, b[1]))
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      fields={'ref': (JCX + 3.81, JCY - 1.27, 0, 'left'), 'val': (JCX + 3.81, JCY + 1.27, 0, 'left')})
W(P('Q203', 'D'), P('J202', 1))
W(P('J202', 2), (281.94, P('J202', 2)[1]), (281.94, P('J202', 2)[1] + 5.08))
s.label('BATN', (281.94, P('J202', 2)[1] + 5.08), 270)
flag('#FLG206', (281.94, P('J202', 2)[1] + 2.54), 90)
s.text('cell +', (JCX + 3.81, JCY - 3.81), 1.27, False)
# DW01A + FS8205A in the negative lead
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gd = P('U204', 'GND')
W(gd, (259.08, gd[1]), (259.08, 106.68))
W(P('C206', 2), (254.0, 106.68), (259.08, 106.68))
s.label('BATN', (254.0, 106.68), 180)
s.nc(P('U204', 'TD'))
FX, FY = 271.78, 124.46
s.add('lcsc:FS8205A_C2830320', 'U205', FX, FY, 0, 'FS8205A', 'lcsc:SOT-23-6_L2.9-W1.6-P0.95-LS2.8-BR',
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W(p3, (p3[0], 185.42), (p3[0] + 5.08, 185.42))
gnd((p3[0] + 5.08, 185.42), 'right')
W(p2, (p2[0], 175.26), (233.68, 175.26), (233.68, en[1]), en)
s.label('EN_3V3', (226.06, 175.26))
R('R221', 236.22, 167.64, '100k', fields=lside(236.22, 167.64))
W((233.68, 175.26), (236.22, 175.26), P('R221', 2))
gnd(P('R221', 1), 'up')
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C('C212', 236.22, lin[1] + 5.08, '1uF', fields=lside(236.22, lin[1] + 5.08))
gnd(P('C212', 2))
W(len_, (241.3, len_[1]), (241.3, len_[1] + 5.08))
s.label('EN_3V3', (241.3, len_[1] + 5.08), 270)
W(lout, (269.24, lout[1]))
C('C213', 264.16, lout[1] + 5.08, '1uF')
gnd(P('C213', 2))
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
